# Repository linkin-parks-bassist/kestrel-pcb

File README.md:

# Kestrel PCB

## Overview

This repository contains the KiCad design files for the main PCB used in Kestrel. The board integrates power distribution, audio I/O, and connectors for the Kestrel Core DSP module, Kestrel Interface control module, and a 5" LCD interface.

The PCB serves as the main carrier board for the system, providing regulated power rails, audio input/output stages, and interconnects between the DSP core, UI processor, and display.

## Dependencies

The board is designed to be used with the following additional components:

- Sipeed Tang Nano 20K (FPGA DSP core)
- Waveshare ESP32-P4-Pico (UI / control processor)
- Waveshare DSI-TOUCH-5A (5" MIPI-DSI display, connected to the ESP32-P4)
- Adafruit MPM3610 5V buck converter breakout

Note: the 5 V rail is currently generated using an external MPM3610 buck module. The PCB is designed so this can be replaced by an integrated regulator in a future revision.

## Power

The board is powered from a standard ***Center negative*** **9 V pedal supply**. The external buck module generates a 5V rail, from which the remaining rails are derived:

- 5 V (buck converter)
- 3.3 V 
- 1.8 V

## Project status

Prototype / Rev A. The design has not yet been manufactured and may change significantly.

## Files

This repository contains:

- KiCad schematic and PCB layout
- fabrication outputs (Gerbers, drill files) *to be added*
- board renders and screenshots

## Related projects

This board is part of Kestrel. Other repos in this project include

- [Main repo](https://github.com/linkin-parks-bassist/kestrel)
- [MCU repo](https://github.com/linkin-parks-bassist/kestrel-interface)
- [FPGA repo](https://github.com/linkin-parks-bassist/kestrel-core)

## License

GNU GPL 3.0

## Contact

I'd love to hear from you.  
email: davidjfarrell96@gmail.com

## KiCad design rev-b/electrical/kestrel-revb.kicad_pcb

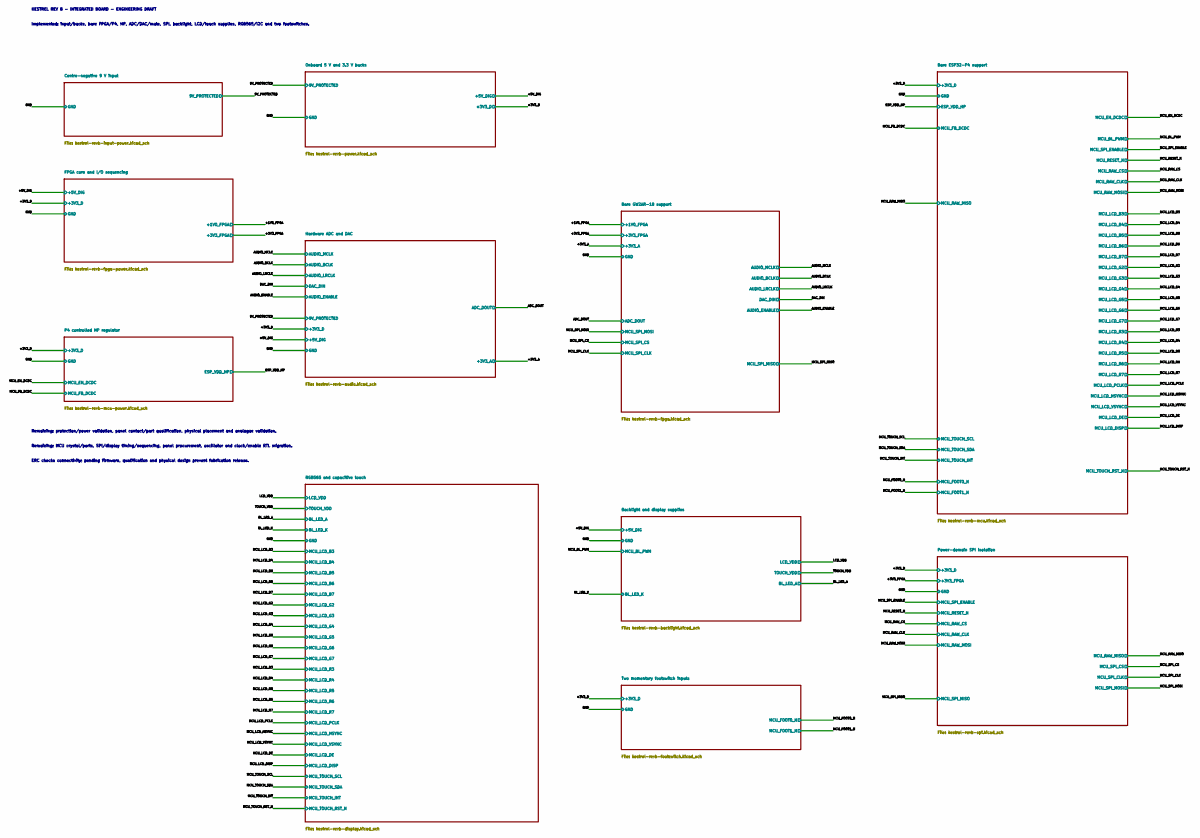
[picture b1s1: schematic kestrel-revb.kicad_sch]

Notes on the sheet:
KESTREL REV B - INTEGRATED BOARD - ENGINEERING DRAFT
Implemented: input/bucks, bare FPGA/P4, HP, ADC/DAC/mute, SPI, backlight, LCD/touch supplies, RGB565/I2C and two footswitches.
Remaining: protection/power validation, panel contact/part qualification, physical placement and analogue validation.
Remaining: MCU crystal/parts, SPI/display timing/sequencing, panel procurement, oscillator and clock/enable RTL migration.
ERC checks connectivity; pending firmware, qualification and physical design prevent fabrication release.

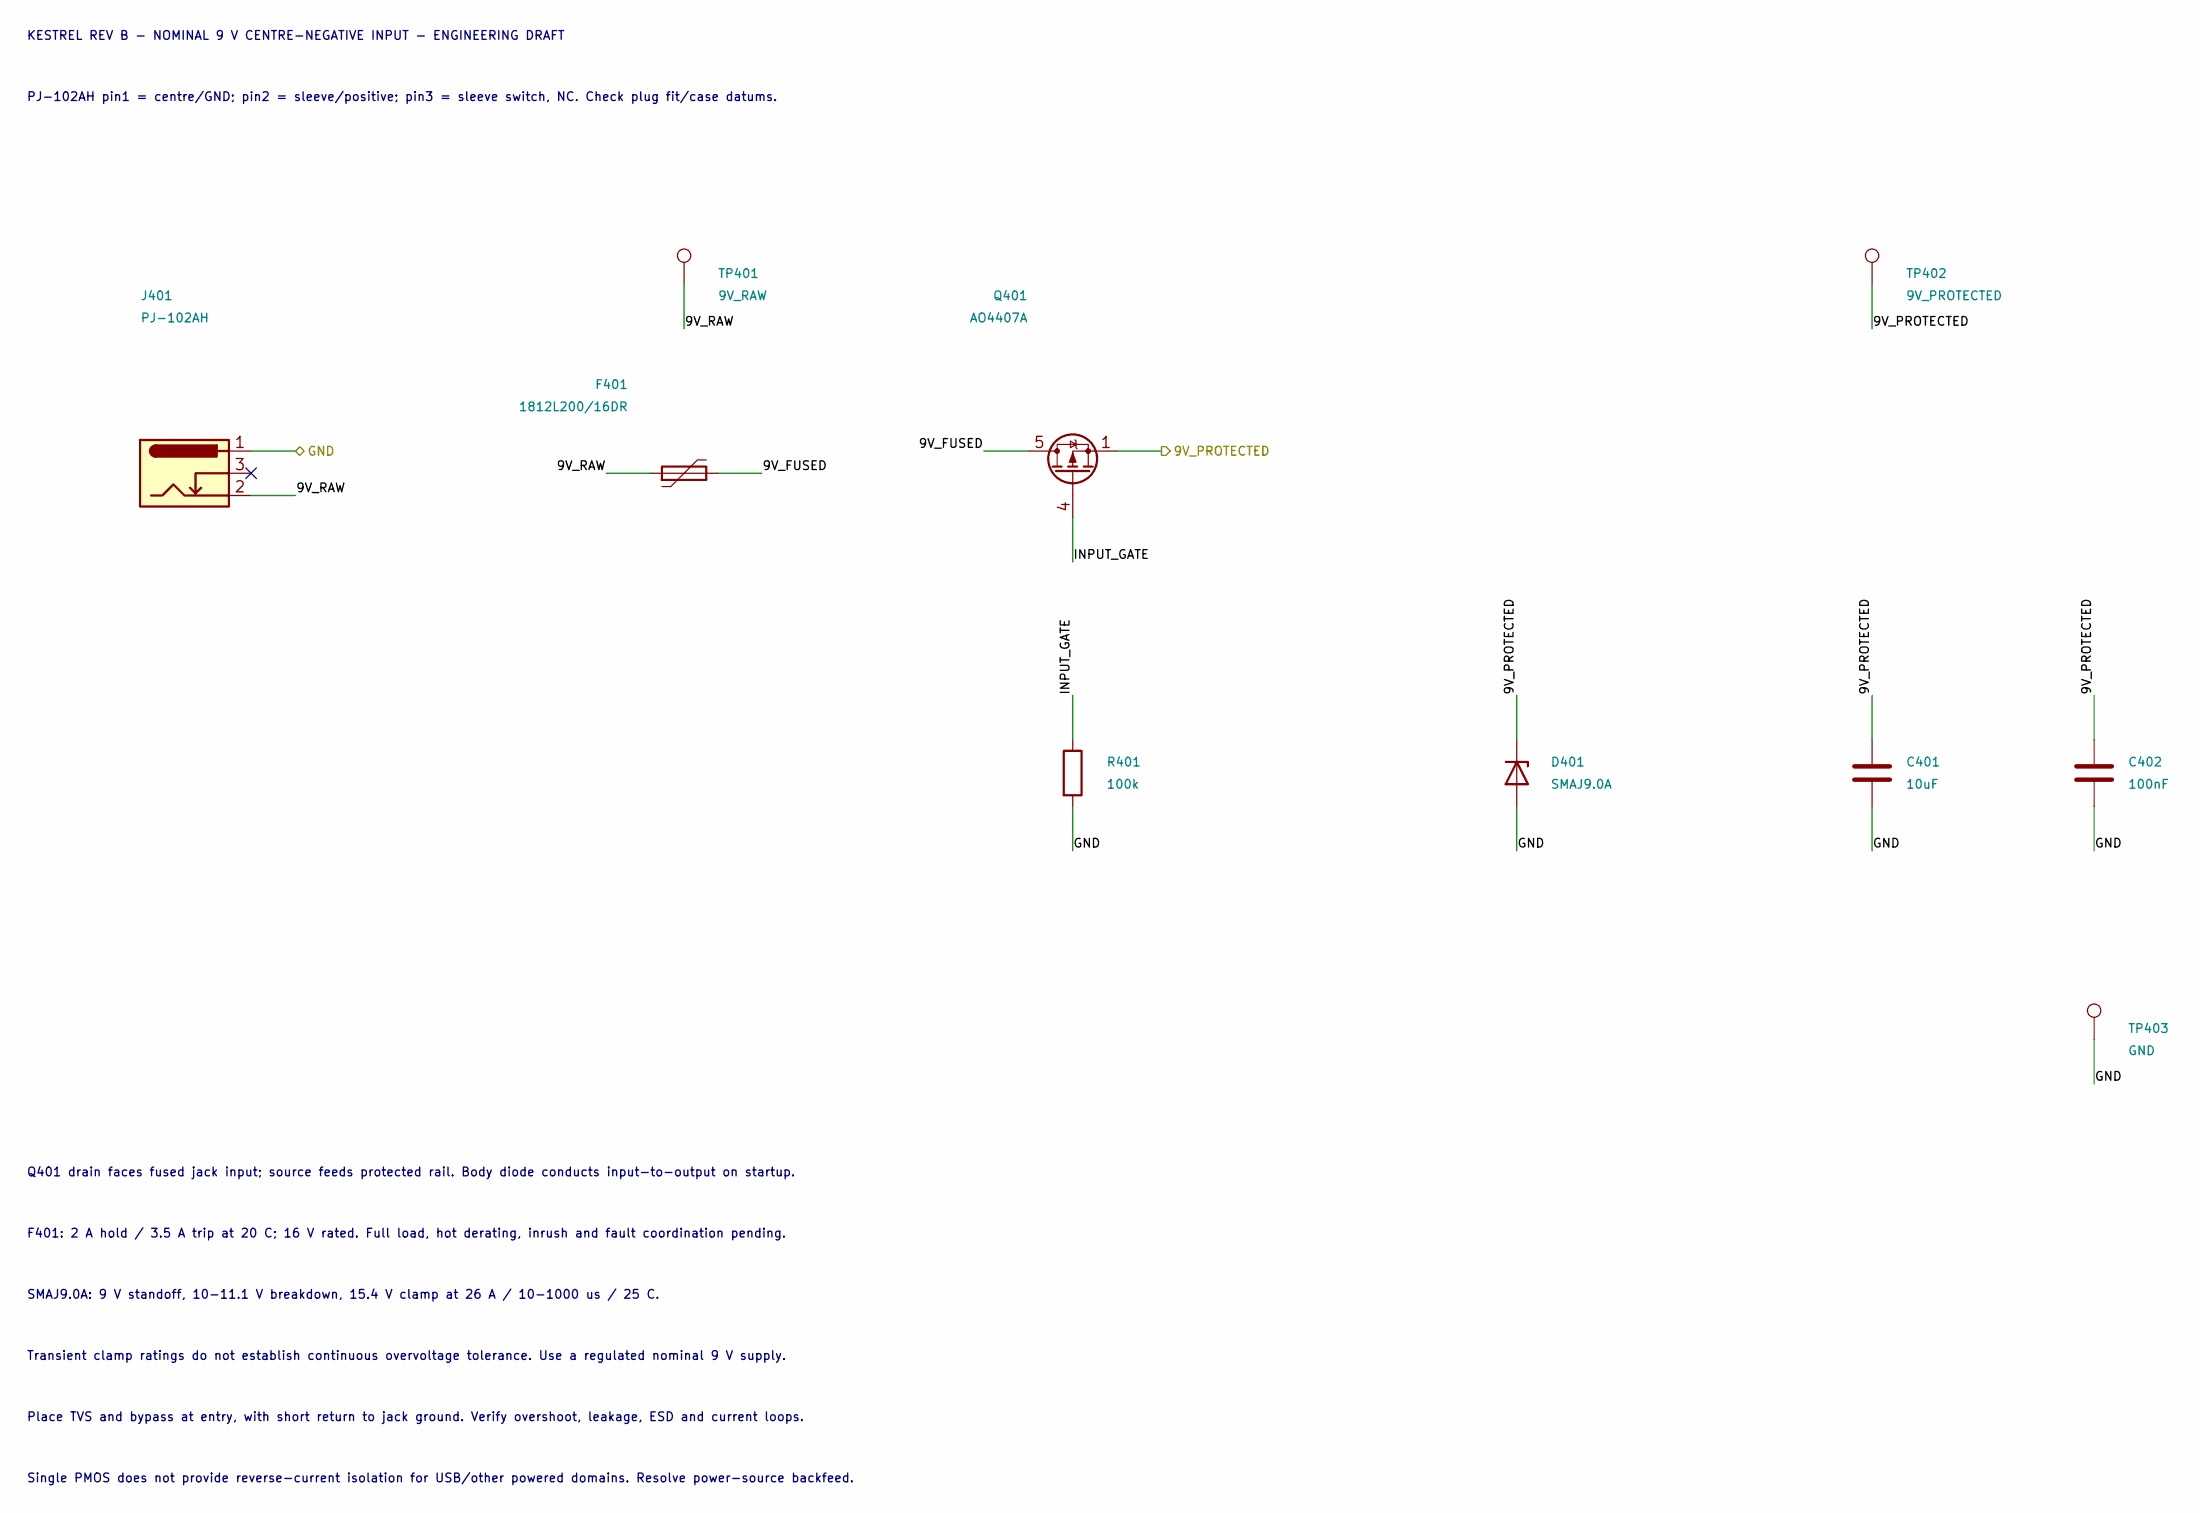
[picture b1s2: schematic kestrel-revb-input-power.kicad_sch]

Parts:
C401: 10uF; C_1210_3225Metric; Rating 10uF / 35V X7R
C402: 100nF; C_0603_1608Metric; Rating 100nF / 50V X7R
D401: SMAJ9.0A; D_SMA
F401: 1812L200/16DR; Fuse_1812_4532Metric
J401: PJ-102AH; BarrelJack_CUI_PJ-102AH_Horizontal
Q401: AO4407A; SOIC-8_3.9x4.9mm_P1.27mm
R401: 100k; R_0603_1608Metric; Rating 100k / 1%
TP401: 9V_RAW; TestPoint_Pad_D1.0mm
TP402: 9V_PROTECTED; TestPoint_Pad_D1.0mm
TP403: GND; TestPoint_Pad_D1.0mm

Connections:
/9V_PROTECTED: C401.1, C402.1, D401.1 (K), Q401.1 (S), Q401.2 (S), Q401.3 (S), TP402.1; also elsewhere on the board
/Centre-negative 9 V input/9V_FUSED: F401.2, Q401.5 (D), Q401.6 (D), Q401.7 (D), Q401.8 (D)
/Centre-negative 9 V input/9V_RAW: F401.1, J401.2, TP401.1
/Centre-negative 9 V input/INPUT_GATE: Q401.4 (G), R401.1
/GND: C401.2, C402.2, D401.2 (A), J401.1, R401.2, TP403.1; also elsewhere on the board

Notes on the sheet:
KESTREL REV B - NOMINAL 9 V CENTRE-NEGATIVE INPUT - ENGINEERING DRAFT
PJ-102AH pin1 = centre/GND; pin2 = sleeve/positive; pin3 = sleeve switch, NC. Check plug fit/case datums.
Q401 drain faces fused jack input; source feeds protected rail. Body diode conducts input-to-output on startup.
F401: 2 A hold / 3.5 A trip at 20 C; 16 V rated. Full load, hot derating, inrush and fault coordination pending.
SMAJ9.0A: 9 V standoff, 10-11.1 V breakdown, 15.4 V clamp at 26 A / 10-1000 us / 25 C.
Transient clamp ratings do not establish continuous overvoltage tolerance. Use a regulated nominal 9 V supply.
Place TVS and bypass at entry, with short return to jack ground. Verify overshoot, leakage, ESD and current loops.
Single PMOS does not provide reverse-current isolation for USB/other powered domains. Resolve power-source backfeed.

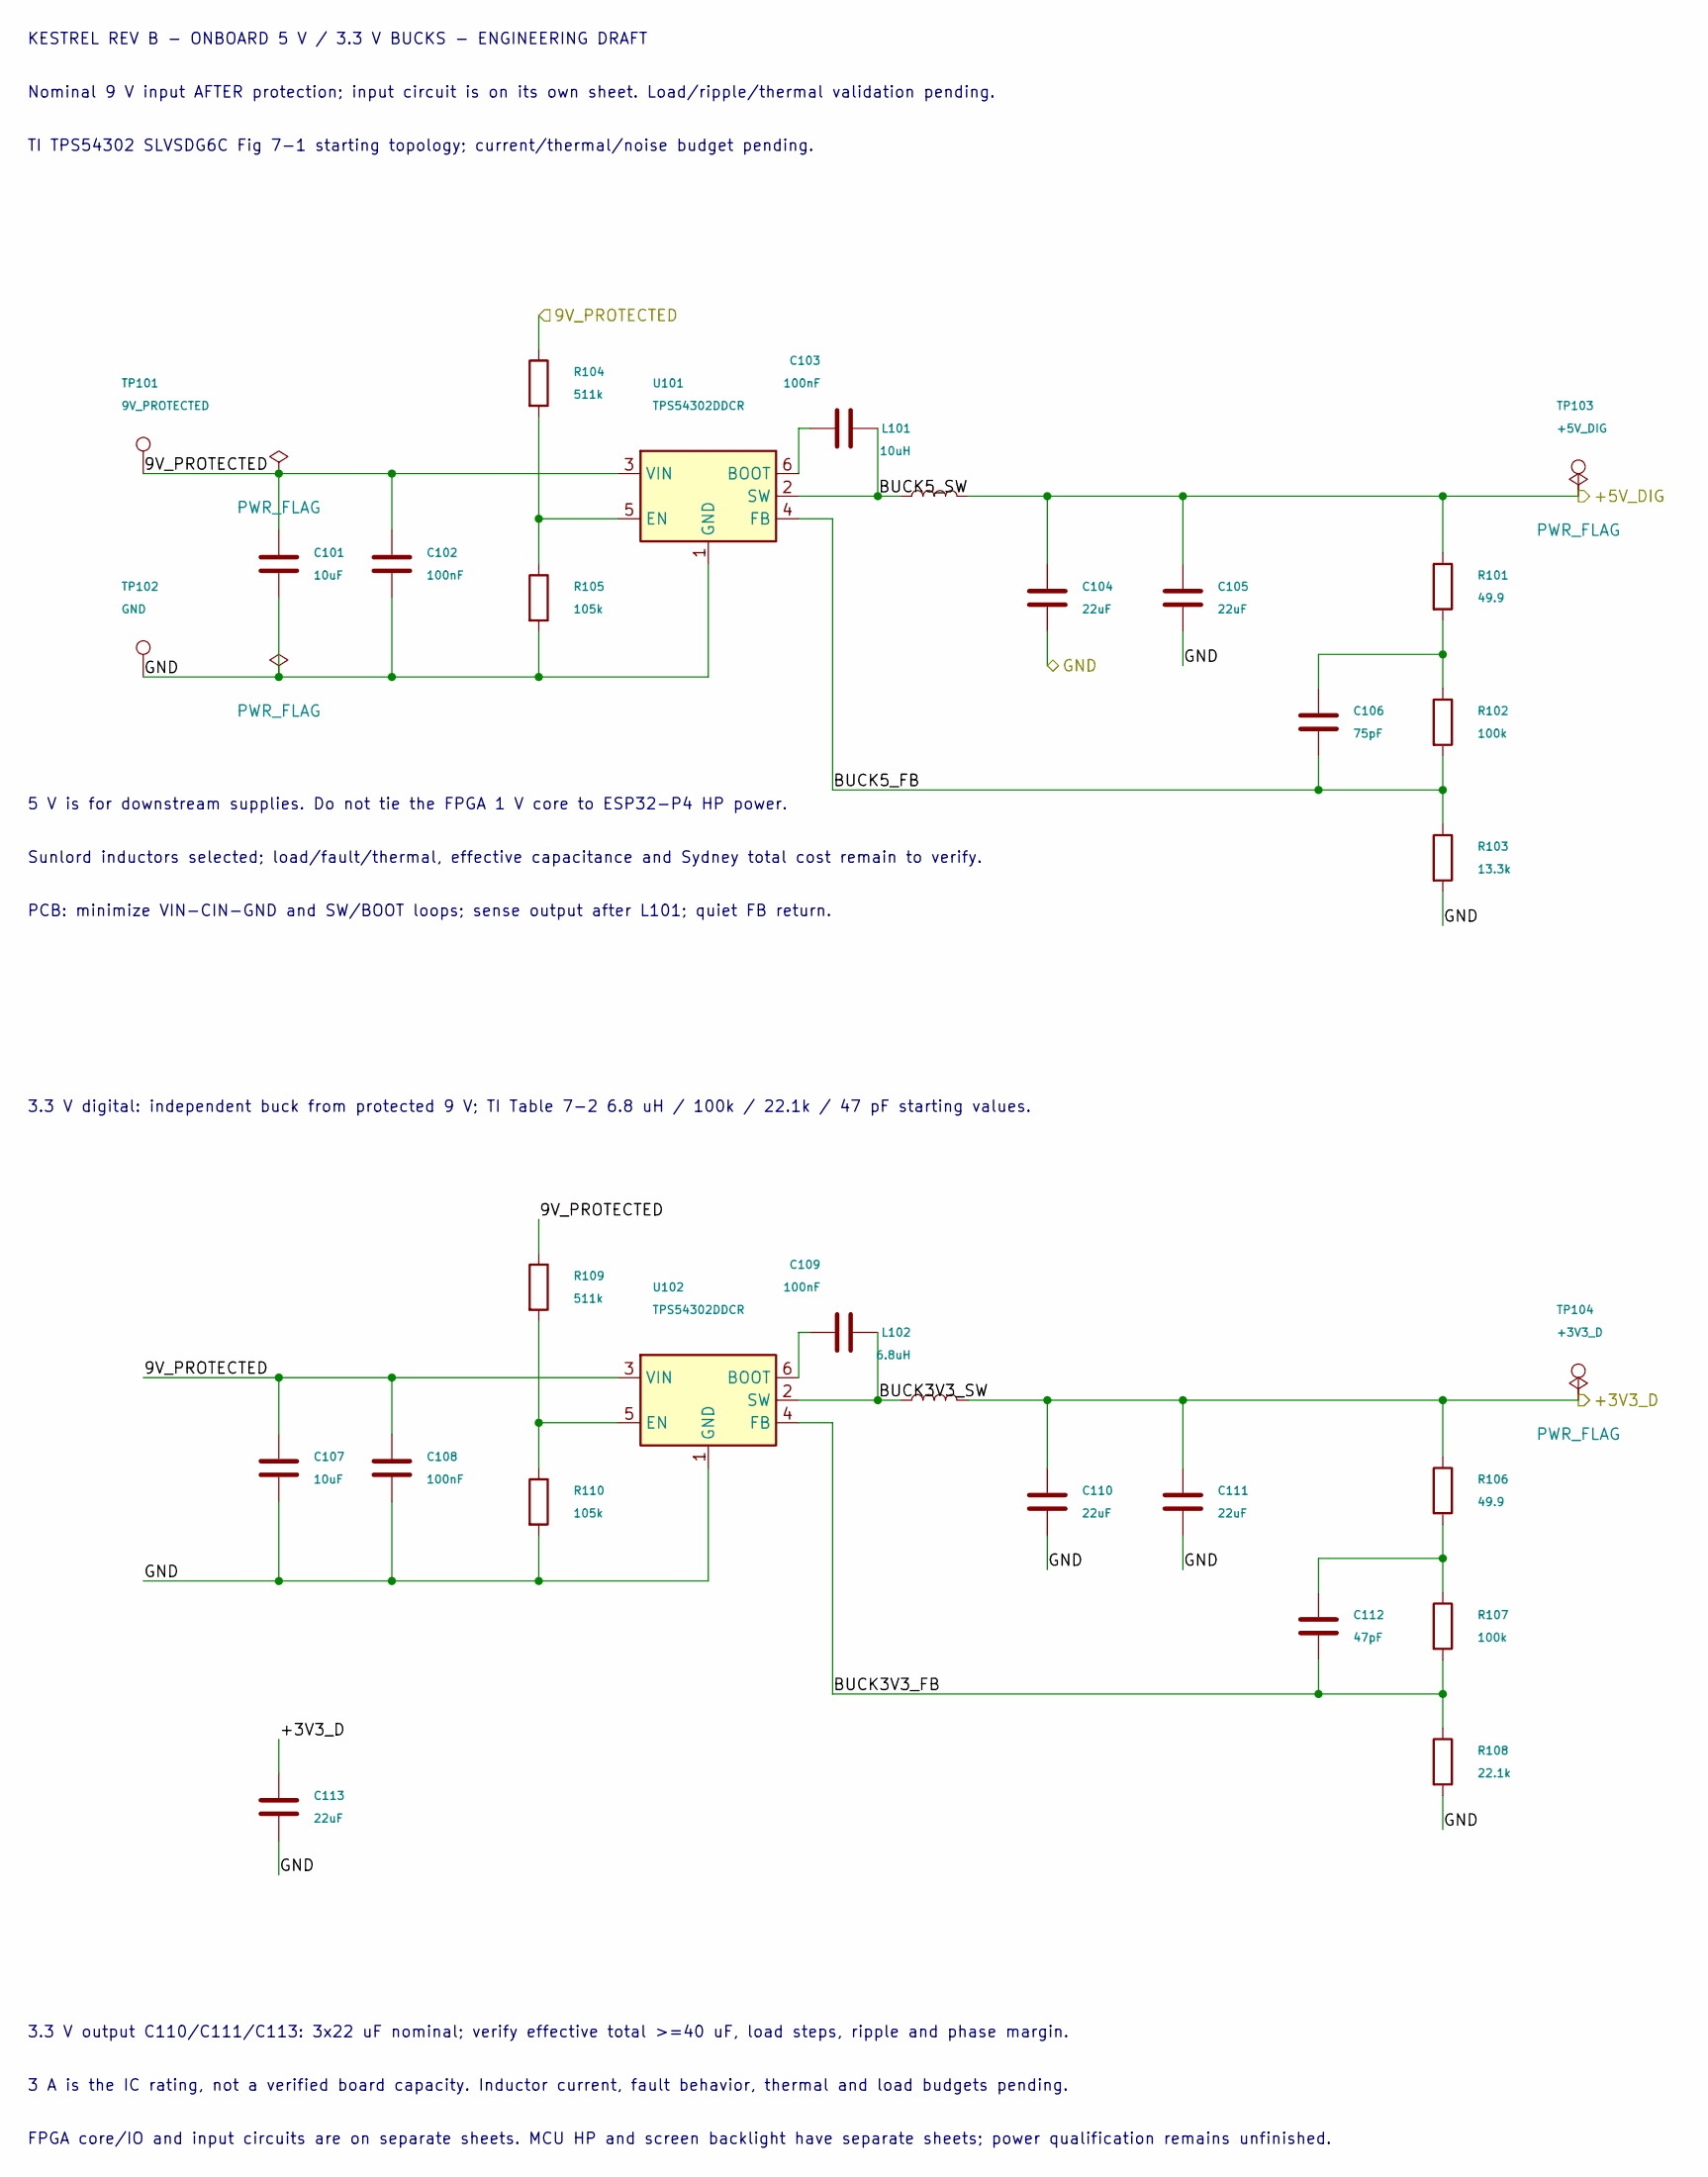
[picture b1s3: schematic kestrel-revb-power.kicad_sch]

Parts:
C101, C107: 10uF; C_1210_3225Metric; Rating 10uF / 35V X7R
C102, C103, C108, C109: 100nF; C_0603_1608Metric; Rating 100nF / 25V
C104, C105, C110, C111, C113: 22uF; C_1210_3225Metric; Rating 22uF / 25V X7R
C106: 75pF; C_0603_1608Metric; Rating 75pF / C0G
C112: 47pF; C_0603_1608Metric; Rating 47pF / C0G
L101: 10uH; L_Sunlord_MWSA0603S; Rating 10uH / Isat >= 4.3A / shielded; MPN MWSA0603S-100MT; LCSC C132141
L102: 6.8uH; L_Sunlord_MWSA0603S; Rating 6.8uH / Isat >= 4.3A / shielded; MPN MWSA0603S-6R8MT; LCSC C408449
R101, R106: 49.9; R_0603_1608Metric; Rating 49.9 / 1%
R102: 100k; R_0603_1608Metric; Rating 100k / 1%
R103: 13.3k; R_0603_1608Metric; Rating 13.3k / 1%
R104, R109: 511k; R_0603_1608Metric; Rating 511k / 1%
R105, R110: 105k; R_0603_1608Metric; Rating 105k / 1%
R107: 100k; R_0603_1608Metric; Rating 100k / 0.1%
R108: 22.1k; R_0603_1608Metric; Rating 22.1k / 0.1%
TP101: 9V_PROTECTED; TestPoint_Pad_D1.0mm
TP102: GND; TestPoint_Pad_D1.0mm
TP103: +5V_DIG; TestPoint_Pad_D1.0mm
TP104: +3V3_D; TestPoint_Pad_D1.0mm
U101, U102: TPS54302DDCR; SOT-23-6

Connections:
/9V_PROTECTED: C101.1, C102.1, C107.1, C108.1, R104.1, R109.1, TP101.1, U101.3 (VIN), U102.3 (VIN); also elsewhere on the board
/+3V3_D: C110.1, C111.1, C113.1, L102.2, R106.1, TP104.1; also elsewhere on the board
/+5V_DIG: C104.1, C105.1, L101.2, R101.1, TP103.1; also elsewhere on the board
/GND: C101.2, C102.2, C104.2, C105.2, C107.2, C108.2, C110.2, C111.2, C113.2, R103.2, R105.2, R108.2, R110.2, TP102.1, U101.1 (GND), U102.1 (GND); also elsewhere on the board
/Onboard 5 V and 3.3 V bucks/BUCK3V3_FB: C112.2, R107.2, R108.1, U102.4 (FB)
/Onboard 5 V and 3.3 V bucks/BUCK3V3_SW: C109.2, L102.1, U102.2 (SW)
/Onboard 5 V and 3.3 V bucks/BUCK5_FB: C106.2, R102.2, R103.1, U101.4 (FB)
/Onboard 5 V and 3.3 V bucks/BUCK5_SW: C103.2, L101.1, U101.2 (SW)
unnamed: C106.1, R101.2, R102.1
unnamed: C112.1, R106.2, R107.1
unnamed: C103.1, U101.6 (BOOT)
unnamed: R104.2, R105.1, U101.5 (EN)
unnamed: C109.1, U102.6 (BOOT)
unnamed: R109.2, R110.1, U102.5 (EN)

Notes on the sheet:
KESTREL REV B - ONBOARD 5 V / 3.3 V BUCKS - ENGINEERING DRAFT
Nominal 9 V input AFTER protection; input circuit is on its own sheet. Load/ripple/thermal validation pending.
TI TPS54302 SLVSDG6C Fig 7-1 starting topology; current/thermal/noise budget pending.
5 V is for downstream supplies. Do not tie the FPGA 1 V core to ESP32-P4 HP power.
Sunlord inductors selected; load/fault/thermal, effective capacitance and Sydney total cost remain to verify.
PCB: minimize VIN-CIN-GND and SW/BOOT loops; sense output after L101; quiet FB return.
3.3 V digital: independent buck from protected 9 V; TI Table 7-2 6.8 uH / 100k / 22.1k / 47 pF starting values.
3.3 V output C110/C111/C113: 3x22 uF nominal; verify effective total >=40 uF, load steps, ripple and phase margin.
3 A is the IC rating, not a verified board capacity. Inductor current, fault behavior, thermal and load budgets pending.
FPGA core/IO and input circuits are on separate sheets. MCU HP and screen backlight have separate sheets; power qualification remains unfinished.
